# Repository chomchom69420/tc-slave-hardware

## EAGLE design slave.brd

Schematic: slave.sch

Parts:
3V1, 3V2, 3V3, 3V4, 3V5, 3V6, 3V7, 3V8, 3V9, 3V10, 3V11, 3V12, 3V13, 3V14, 3V15, 3V16, 3V17, 3V18, 3V19, 3V21: MCP40D17T-503E/LT; SC70-6_MC_MCH
C2: 100pF; C0603
C3, C4: 10uF; C0805
C5: 1uF; C0603
CB: 100nF; C0603
CEN, CEN1, CEN2, CEN3, CEN4, CEN5, CEN6, CEN7, CEN8, CEN9, CEN10, CEN11, CEN12, CEN13, CEN14, CEN15, CEN16, CEN17, CEN18, CEN19, CEN20: 100nF; C0603
CIN1, CIN2, CIN3: 10uF; C0805
COUT1, COUT2, COUT3, COUT4: 22uF; C1206
CSS: 47nF; C0603
CTON: 100pF; C0402
CVC: 4.7uF; C0402
D1, D2, D3, D4, D5, D6, D7, D11, D12, D13, D14, D15, D16, D17, D18, D19, D20, D21, D22, D23, D24, D25, D26, D27, D28, D29, D30, D31, D32, D33, D34, D35, D36, D37, D38, D39, D40, D41, D42, D43, D44, D45: VLMY1500-GS08; LED_1500-GS08_VIS
DEN: BZX84C5V1-7-F; SOT23
EN: CONN_HDR_1POS_0.1; 1X1
ESP_HDR_LEFT: PPTC191LFBN-RC; RHDR19W80P0X254_1X19_4876X254X
ESP_HDR_RIGHT: PPTC191LFBN-RC; RHDR19W80P0X254_1X19_4876X254X
FB: CONN_HDR_1POS_0.1; 1X1
J2, J3, J4, J5: EB21A-06-D; CONN_EB21A-06-D_ADM
J6, J7, J8: 282837-9; TE_282837-9
J9: 1715250000; CONN2_250000_WED
L1: 1.5uH; BCIH1367-2R2M
LX: CONN_HDR_1POS_0.1; 1X1
Q1, Q2, Q3, Q4, Q5, Q7, Q8, Q9, Q10, Q11, Q12, Q13, Q14, Q15, Q16, Q17, Q18, Q19, Q20, Q21, Q22, Q23, Q24, Q25, Q26, Q27, Q28, Q29, Q30, Q31, Q32, Q33, Q34, Q35, Q36, Q37, Q38, Q39, Q40, Q41, Q42: DMN2056U-7; SOT23
R1: 5.1k; R0603
R2: 27k; R0603
R3: 1k; R0402
R4, R8, R11, R12, R15, R19, R24, R28, R34, R37, R40, R43, R46, R49, R52, R55, R58, R61, R64, R67, R70, R73, R76, R79, R82, R85, R88, R91, R94, R97, R100, R103, R106, R109, R112, R115, R118, R121, R124, R127, R130: 220; R0603
R5, R6, R9, R13, R17, R20, R26, R29, R35, R38, R41, R44, R47, R50, R53, R56, R59, R62, R65, R68, R71, R74, R77, R80, R83, R86, R89, R92, R95, R98, R101, R104, R107, R110, R113, R116, R119, R122, R125, R128, R131: 150; R0603
R7, R10, R14, R18, R21, R25, R27, R30, R36, R39, R42, R45, R48, R51, R54, R57, R60, R63, R66, R69, R72, R75, R78, R81, R84, R87, R90, R93, R96, R99, R102, R105, R108, R111, R114, R117, R120, R123, R126, R129, R132: 6.8k; R0603
R16: 100R; PR-D2.7XL8.5MM
R22, R23: 0R; R0402
R31: 100k; R0402
R32, R33, R133, R134, R135, R136, R137, R138, R139, R140, R141, R142, R143, R144, R145, R146, R147, R148, R149, R171: CR-02JL6----1K; RES_CR-02_VKG
R169: RC0402FR-07698KL; RESC1005X40N
R170: RC0402FR-0782K5L; RC0402N_YAG
RECT: DBF310-13; DBF_DIO
REG: AOZ2255EQI-30; QFN_4X4_22L-EP2_S_AOS
REN: 1k; R0603
TON: CONN_HDR_1POS_0.1; 1X1
TP1, TP4, TP5: TPB1,27; B1,27
U1, U10, U11, U12, U13, U14, U15, U16, U17, U18, U19, U20, U21, U22, U23, U24, U25, U26, U27, U28: INA332AIDGKR; DGK0008A_N
U2: AP2112K-3.3TRG1; SOT_RG1_DIO
U3, U4, U5: MCP23008-E/P; DIP254P762X533-18
U6, U7, U8, U9: MC74HCT4851ADR2G; SOIC-16_ONS
U$1, U$2, U$4, U$5, U$6, U$7, U$8, U$9, U$10, U$11, U$12, U$13, U$14, U$15, U$16, U$17, U$18, U$19, U$20, U$21: YLR12-2-100F
VIN: CONN_HDR_1POS_0.1; 1X1

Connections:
3V3: 3V1.1 (VDD), 3V2.1 (VDD), 3V3.1 (VDD), 3V4.1 (VDD), 3V5.1 (VDD), 3V6.1 (VDD), 3V7.1 (VDD), 3V8.1 (VDD), 3V9.1 (VDD), 3V10.1 (VDD), 3V11.1 (VDD), 3V12.1 (VDD), 3V13.1 (VDD), 3V14.1 (VDD), 3V15.1 (VDD), 3V16.1 (VDD), 3V17.1 (VDD), 3V18.1 (VDD), 3V19.1 (VDD), 3V21.1 (VDD), C4.2, C5.2, ESP_HDR_LEFT.19, TP5.TP, U2.5 (VOUT)
5V0: ESP_HDR_LEFT.1
+5V: C2.2, C3.2, CEN1.2, CEN2.2, CEN3.2, CEN4.2, CEN5.2, CEN6.2, CEN7.2, CEN8.2, CEN9.2, CEN10.2, CEN11.2, CEN12.2, CEN13.2, CEN14.2, CEN15.2, CEN16.2, CEN17.2, CEN18.2, CEN19.2, CEN20.2, COUT1.2, COUT2.2, COUT3.2, COUT4.2, L1.P$2 (2), R2.1, R3.2, R16.2, R31.2, TP1.TP, U1.7 (V+), U1.8 (SD), U2.1 (VIN), U3.6 (*RESET), U3.18 (VDD), U4.5 (A0), U4.6 (*RESET), U4.18 (VDD), U5.4 (A1), U5.6 (*RESET), U5.18 (VDD), U6.16 (VCC), U7.16 (VCC), U8.16 (VCC), U9.16 (VCC), U10.7 (V+), U10.8 (SD), U11.7 (V+), U11.8 (SD), U12.7 (V+), U12.8 (SD), U13.7 (V+), U13.8 (SD), U14.7 (V+), U14.8 (SD), U15.7 (V+), U15.8 (SD), U16.7 (V+), U16.8 (SD), U17.7 (V+), U17.8 (SD), U18.7 (V+), U18.8 (SD), U19.7 (V+), U19.8 (SD), U20.7 (V+), U20.8 (SD), U21.7 (V+), U21.8 (SD), U22.7 (V+), U22.8 (SD), U23.7 (V+), U23.8 (SD), U24.7 (V+), U24.8 (SD), U25.7 (V+), U25.8 (SD), U26.7 (V+), U26.8 (SD), U27.7 (V+), U27.8 (SD), U28.7 (V+), U28.8 (SD)
+12V: J9.2, RECT.2
BST: CB.2, REG.20 (BST)
CS_SEL0: ESP_HDR_LEFT.5, U6.11 (A), U7.11 (A), U8.11 (A), U9.11 (A)
CS_SEL1: ESP_HDR_LEFT.7, U6.10 (B), U7.10 (B), U8.10 (B), U9.10 (B)
CS_SEL2: ESP_HDR_LEFT.8, U6.9 (C), U7.9 (C), U8.9 (C), U9.9 (C)
D0_A: R70.2, R71.2, U3.10 (GP0)
D0_A+: J8.8, Q22.P$2 (S)
D0_B: R73.2, R74.2, U3.11 (GP1)
D0_B+: J8.7, Q23.P$2 (S)
D0_C: R76.2, R77.2, U3.12 (GP2)
D0_C+: J8.6, Q24.P$2 (S)
D0_D: R79.2, R80.2, U3.13 (GP3)
D0_D+: J8.5, Q25.P$2 (S)
D0_E: R82.2, R83.2, U3.14 (GP4)
D0_E+: J8.4, Q26.P$2 (S)
D0_F: R100.2, R101.2, U3.15 (GP5)
D0_F+: J8.3, Q32.P$2 (S)
D0_G: R103.2, R104.2, U3.16 (GP6)
D0_G+: J8.2, Q33.P$2 (S)
D1_A: R85.2, R86.2, U4.10 (GP0)
D1_A+: J6.8, Q27.P$2 (S)
D1_B: R88.2, R89.2, U4.11 (GP1)
D1_B+: J6.7, Q28.P$2 (S)
D1_C: R91.2, R92.2, U4.12 (GP2)
D1_C+: J6.6, Q29.P$2 (S)
D1_D: R94.2, R95.2, U4.13 (GP3)
D1_D+: J6.5, Q30.P$2 (S)
D1_E: R97.2, R98.2, U4.14 (GP4)
D1_E+: J6.4, Q31.P$2 (S)
D1_F: R106.2, R107.2, U4.15 (GP5)
D1_F+: J6.3, Q34.P$2 (S)
D1_G: R109.2, R110.2, U4.16 (GP6)
D1_G+: J6.2, Q35.P$2 (S)
D2_A: R112.2, R113.2, U5.10 (GP0)
D2_A+: J7.8, Q36.P$2 (S)
D2_B: R115.2, R116.2, U5.11 (GP1)
D2_B+: J7.7, Q37.P$2 (S)
D2_C: R118.2, R119.2, U5.12 (GP2)
D2_C+: J7.6, Q38.P$2 (S)
D2_D: R121.2, R122.2, U5.13 (GP3)
D2_D+: J7.5, Q39.P$2 (S)
D2_E: R124.2, R125.2, U5.14 (GP4)
D2_E+: J7.4, Q40.P$2 (S)
D2_F: R127.2, R128.2, U5.15 (GP5)
D2_F+: J7.3, Q41.P$2 (S)
D2_G: R130.2, R131.2, U5.16 (GP6)
D2_G+: J7.2, Q42.P$2 (S)
EN: CEN.2, DEN.P$3 (C), EN.1, REG.1 (EN), REN.2
EN_F: R31.1, U2.3 (EN)
ESP_EN: ESP_HDR_LEFT.18
FB: FB.1, R1.1, R2.2, REG.2 (FB)
GND: 3V1.2 (VSS), 3V2.2 (VSS), 3V3.2 (VSS), 3V4.2 (VSS), 3V5.2 (VSS), 3V6.2 (VSS), 3V7.2 (VSS), 3V8.2 (VSS), 3V9.2 (VSS), 3V10.2 (VSS), 3V11.2 (VSS), 3V12.2 (VSS), 3V13.2 (VSS), 3V14.2 (VSS), 3V15.2 (VSS), 3V16.2 (VSS), 3V17.2 (VSS), 3V18.2 (VSS), 3V19.2 (VSS), 3V21.2 (VSS), C2.1, C3.1, C4.1, C5.1, CEN.1, CEN1.1, CEN2.1, CEN3.1, CEN4.1, CEN5.1, CEN6.1, CEN7.1, CEN8.1, CEN9.1, CEN11.1, CEN12.1, CEN13.1, CEN14.1, CEN15.1, CEN16.1, CEN17.1, CEN18.1, CEN19.1, CEN20.1, CIN1.1, CIN2.1, CIN3.1, COUT1.1, COUT2.1, COUT3.1, COUT4.1, CSS.2, CTON.2, CVC.2, D7.1, DEN.P$1 (A), ESP_HDR_LEFT.6, ESP_HDR_RIGHT.13, ESP_HDR_RIGHT.19, J2.1, J3.1, J4.1, J5.1, J6.1, J7.1, J8.1, R1.2, R7.1, R10.1, R14.1, R16.1, R18.1, R21.1, R23.1, R25.1, R27.1, R30.1, R36.1, R39.1, R42.1, R45.1, R48.1, R51.1, R54.1, R57.1, R60.1, R63.1, R66.1, R69.1, R72.1, R75.1, R78.1, R81.1, R84.1, R87.1, R90.1, R93.1, R96.1, R99.1, R102.1, R105.1, R108.1, R111.1, R114.1, R117.1, R120.1, R123.1, R126.1, R129.1, R132.1, RECT.3, REG.3 (AGND), REG.12 (PGND_2), REG.13 (PGND_3), REG.14 (PGND_4), REG.15 (PGND), TP4.TP, U1.4 (V-), U2.2 (GND), U3.3 (A2), U3.4 (A1), U3.5 (A0), U3.9 (VSS), U4.3 (A2), U4.4 (A1), U4.9 (VSS), U5.3 (A2), U5.5 (A0), U5.9 (VSS), U6.2 (X6), U6.4 (X7), U6.5 (X5), U6.6 (ENABLE), U6.8 (GND), U7.2 (X6), U7.4 (X7), U7.5 (X5), U7.6 (ENABLE), U7.8 (GND), U8.2 (X6), U8.4 (X7), U8.5 (X5), U8.6 (ENABLE), U8.8 (GND), U9.2 (X6), U9.4 (X7), U9.5 (X5), U9.6 (ENABLE), U9.8 (GND), U10.4 (V-), U11.4 (V-), U12.4 (V-), U13.4 (V-), U14.4 (V-), U15.4 (V-), U16.4 (V-), U17.4 (V-), U18.4 (V-), U19.4 (V-), U20.4 (V-), U21.4 (V-), U22.4 (V-), U23.4 (V-), U24.4 (V-), U25.4 (V-), U26.4 (V-), U27.4 (V-), U28.4 (V-)
GPIO1: ESP_HDR_RIGHT.16
GPIO3: ESP_HDR_RIGHT.15
GPIO6: ESP_HDR_RIGHT.1
GPIO7: ESP_HDR_RIGHT.2
GPIO8: ESP_HDR_RIGHT.3
GPIO9: ESP_HDR_LEFT.4
GPIO10: ESP_HDR_LEFT.3
GPIO11: ESP_HDR_LEFT.2
I_OA: 3V17.6 (W), U7.14 (X1), U26.6 (VOUT)
I_OGF: 3V6.6 (W), U7.15 (X2), U14.6 (VOUT)
I_OGL: 3V18.6 (W), U7.12 (X3), U27.6 (VOUT)
I_OGR: 3V7.6 (W), U7.1 (X4), U15.6 (VOUT)
I_OR: 3V5.6 (W), U7.13 (X0), U13.6 (VOUT)
I_PA: 3V12.6 (W), U6.14 (X1), U21.6 (VOUT)
I_PGF: 3V1.6 (W), U1.6 (VOUT), U6.15 (X2)
I_PGL: 3V13.6 (W), U6.12 (X3), U22.6 (VOUT)
I_PGR: 3V2.6 (W), U6.1 (X4), U10.6 (VOUT)
I_PR: 3V21.6 (W), U6.13 (X0), U19.6 (VOUT)
I_SA: 3V3.6 (W), U8.14 (X1), U11.6 (VOUT)
I_SGF: 3V15.6 (W), U8.15 (X2), U24.6 (VOUT)
I_SGL: 3V4.6 (W), U8.12 (X3), U12.6 (VOUT)
I_SGR: 3V16.6 (W), U8.1 (X4), U25.6 (VOUT)
I_SPA: 3V8.6 (W), U9.14 (X1), U16.6 (VOUT)
I_SPGF: 3V10.6 (W), U9.15 (X2), U18.6 (VOUT)
I_SPGL: 3V9.6 (W), U9.12 (X3), U17.6 (VOUT)
I_SPGR: 3V11.6 (W), U9.1 (X4), U20.6 (VOUT)
I_SPR: 3V19.6 (W), U9.13 (X0), U28.6 (VOUT)
I_SR: 3V14.6 (W), U8.13 (X0), U23.6 (VOUT)
JP2: D1.1, D2.1, D3.1, D4.1, D5.1, D6.1, D11.1, D12.1, D13.1, D14.1, D15.1, D16.1, D17.1, D18.1, D19.1, D20.1, D21.1, D22.1, D23.1, D24.1, D25.1, D26.1, D27.1, D28.1, D29.1, D30.1, D31.1, D32.1, D33.1, D34.1, D35.1, D36.1, D37.1, D38.1, D39.1, D40.1, D41.1, D42.1, D43.1, D44.1, D45.1, R23.2
LX: CB.1, L1.P$1 (1), LX.1, REG.10 (LX_2), REG.16 (LX_3), REG.17 (LX_4), REG.18 (LX)
unnamed: D2.2, R6.1
unnamed: R3.1, R22.2
unnamed: D7.2, R22.1
unnamed: 3V21.5 (B), R171.1, U19.1 (RG)
unnamed: 3V1.5 (B), R32.1, U1.1 (RG)
unnamed: R32.2, U1.5 (REF)
unnamed: D3.2, R9.1
unnamed: J9.1, RECT.4
unnamed: 3V2.5 (B), R33.1, U10.1 (RG)
unnamed: R33.2, U10.5 (REF)
unnamed: 3V3.5 (B), R133.1, U11.1 (RG)
unnamed: R171.2, U19.5 (REF)
unnamed: R133.2, U11.5 (REF)
unnamed: D1.2, R5.1
unnamed: 3V4.5 (B), R134.1, U12.1 (RG)
unnamed: R134.2, U12.5 (REF)
unnamed: D4.2, R13.1
unnamed: 3V5.5 (B), R135.1, U13.1 (RG)
unnamed: R135.2, U13.5 (REF)
unnamed: D5.2, R17.1
unnamed: 3V6.5 (B), R136.1, U14.1 (RG)
unnamed: R136.2, U14.5 (REF)
unnamed: D6.2, R20.1
unnamed: 3V7.5 (B), R137.1, U15.1 (RG)
unnamed: R137.2, U15.5 (REF)
unnamed: D11.2, R26.1
unnamed: 3V8.5 (B), R138.1, U16.1 (RG)
unnamed: R138.2, U16.5 (REF)
unnamed: 3V9.5 (B), R139.1, U17.1 (RG)
unnamed: R139.2, U17.5 (REF)
unnamed: 3V10.5 (B), R140.1, U18.1 (RG)
unnamed: R140.2, U18.5 (REF)
unnamed: 3V11.5 (B), R141.1, U20.1 (RG)
unnamed: R141.2, U20.5 (REF)
unnamed: 3V12.5 (B), R142.1, U21.1 (RG)
unnamed: R142.2, U21.5 (REF)
unnamed: 3V13.5 (B), R143.1, U22.1 (RG)
unnamed: R143.2, U22.5 (REF)
unnamed: 3V14.5 (B), R144.1, U23.1 (RG)
unnamed: R144.2, U23.5 (REF)
unnamed: 3V15.5 (B), R145.1, U24.1 (RG)
unnamed: R145.2, U24.5 (REF)
unnamed: 3V16.5 (B), R146.1, U25.1 (RG)
unnamed: R146.2, U25.5 (REF)
unnamed: 3V17.5 (B), R147.1, U26.1 (RG)
unnamed: R147.2, U26.5 (REF)
unnamed: 3V18.5 (B), R148.1, U27.1 (RG)
unnamed: R148.2, U27.5 (REF)
unnamed: 3V19.5 (B), R149.1, U28.1 (RG)
unnamed: R149.2, U28.5 (REF)
unnamed: R169.1, R170.2
unnamed: D12.2, R29.1
unnamed: D13.2, R35.1
unnamed: D14.2, R38.1
unnamed: D15.2, R41.1
unnamed: D16.2, R44.1
unnamed: D17.2, R47.1
unnamed: D18.2, R50.1
unnamed: D19.2, R53.1
unnamed: D20.2, R56.1
unnamed: D21.2, R59.1
unnamed: D22.2, R62.1
unnamed: D23.2, R65.1
unnamed: D24.2, R68.1
unnamed: D25.2, R71.1
unnamed: D26.2, R74.1
unnamed: D27.2, R77.1
unnamed: D28.2, R80.1
unnamed: D29.2, R83.1
unnamed: D30.2, R86.1
unnamed: D31.2, R89.1
unnamed: D32.2, R92.1
unnamed: D33.2, R95.1
unnamed: D34.2, R98.1
unnamed: D35.2, R101.1
unnamed: D36.2, R104.1
unnamed: D37.2, R107.1
unnamed: D38.2, R110.1
unnamed: D39.2, R113.1
unnamed: D40.2, R116.1
unnamed: D41.2, R119.1
unnamed: D42.2, R122.1
unnamed: D43.2, R125.1
unnamed: D44.2, R128.1
unnamed: D45.2, R131.1
OA+: J4.5, U26.2 (VIN-), U$15.P$2
OA++: Q13.P$2 (S), U26.3 (VIN+), U$15.P$1
OGF+: J4.4, U14.2 (VIN-), U$14.P$2
OGF++: Q14.P$2 (S), U14.3 (VIN+), U$14.P$1
OGL+: J4.3, U27.2 (VIN-), U$13.P$2
OGL++: Q15.P$2 (S), U27.3 (VIN+), U$13.P$1
OGR+: J4.2, U15.2 (VIN-), U$12.P$2
OGR++: Q16.P$2 (S), U15.3 (VIN+), U$12.P$1
OR+: J4.6, U13.2 (VIN-), U$16.P$2
OR++: Q12.P$2 (S), U13.3 (VIN+), U$16.P$1
O_CURRENT: ESP_HDR_LEFT.16, U7.3 (X)
PA: ESP_HDR_LEFT.10, R4.2, R6.2, R43.2, R44.2
PA+: J2.5, U21.2 (VIN-), U$2.P$2
PA++: Q2.P$2 (S), U21.3 (VIN+), U$2.P$1
PGF: ESP_HDR_LEFT.11, R8.2, R9.2, R46.2, R47.2
PGF+: J2.4, U1.2 (VIN-), U$4.P$2
PGF++: Q3.P$2 (S), U1.3 (VIN+), U$4.P$1
PGL: ESP_HDR_LEFT.12, R12.2, R13.2, R49.2, R50.2
PGL+: J2.3, U22.2 (VIN-), U$5.P$2
PGL++: Q4.P$2 (S), U22.3 (VIN+), U$5.P$1
PGR: ESP_HDR_LEFT.13, R15.2, R17.2, R52.2, R53.2
PGR+: J2.2, U10.2 (VIN-), U$6.P$2
PGR++: Q5.P$2 (S), U10.3 (VIN+), U$6.P$1
PR: ESP_HDR_LEFT.9, R5.2, R11.2, R40.2, R41.2
PR+: J2.6, U19.2 (VIN-), U$1.P$2
PR++: Q1.P$2 (S), U19.3 (VIN+), U$1.P$1
P_CURRENT: ESP_HDR_LEFT.14, U6.3 (X)
Q1G: Q1.P$1 (G), R11.1, R25.2
Q1G1: Q2.P$1 (G), R4.1, R7.2
Q1G2: Q3.P$1 (G), R8.1, R10.2
Q1G3: Q4.P$1 (G), R12.1, R14.2
Q1G4: Q5.P$1 (G), R15.1, R18.2
Q1G5: Q7.P$1 (G), R19.1, R21.2
Q1G6: Q8.P$1 (G), R24.1, R27.2
Q1G7: Q9.P$1 (G), R28.1, R30.2
Q1G8: Q10.P$1 (G), R34.1, R36.2
Q1G9: Q11.P$1 (G), R37.1, R39.2
Q1G10: Q12.P$1 (G), R40.1, R42.2
Q1G11: Q13.P$1 (G), R43.1, R45.2
Q1G12: Q14.P$1 (G), R46.1, R48.2
Q1G13: Q15.P$1 (G), R49.1, R51.2
Q1G14: Q16.P$1 (G), R52.1, R54.2
Q1G15: Q17.P$1 (G), R55.1, R57.2
Q1G16: Q18.P$1 (G), R58.1, R60.2
Q1G17: Q19.P$1 (G), R61.1, R63.2
Q1G18: Q20.P$1 (G), R64.1, R66.2
Q1G19: Q21.P$1 (G), R67.1, R69.2
Q1G20: Q22.P$1 (G), R70.1, R72.2
Q1G21: Q23.P$1 (G), R73.1, R75.2
Q1G22: Q24.P$1 (G), R76.1, R78.2
Q1G23: Q25.P$1 (G), R79.1, R81.2
Q1G24: Q26.P$1 (G), R82.1, R84.2
Q1G25: Q27.P$1 (G), R85.1, R87.2
Q1G26: Q28.P$1 (G), R88.1, R90.2
Q1G27: Q29.P$1 (G), R91.1, R93.2
Q1G28: Q30.P$1 (G), R94.1, R96.2
Q1G29: Q31.P$1 (G), R97.1, R99.2
Q1G30: Q32.P$1 (G), R100.1, R102.2
Q1G31: Q33.P$1 (G), R103.1, R105.2
Q1G32: Q34.P$1 (G), R106.1, R108.2
Q1G33: Q35.P$1 (G), R109.1, R111.2
Q1G34: Q36.P$1 (G), R112.1, R114.2
Q1G35: Q37.P$1 (G), R115.1, R117.2
Q1G36: Q38.P$1 (G), R118.1, R120.2
Q1G37: Q39.P$1 (G), R121.1, R123.2
Q1G38: Q40.P$1 (G), R124.1, R126.2
Q1G39: Q41.P$1 (G), R127.1, R129.2
Q1G40: Q42.P$1 (G), R130.1, R132.2
SA: ESP_HDR_RIGHT.9, R24.2, R26.2
SA+: J3.5, U11.2 (VIN-), U$8.P$2
SA++: Q8.P$2 (S), U11.3 (VIN+), U$8.P$1
SCL: 3V1.3 (SCL), 3V2.3 (SCL), 3V3.3 (SCL), 3V4.3 (SCL), 3V5.3 (SCL), 3V6.3 (SCL), 3V7.3 (SCL), 3V8.3 (SCL), 3V9.3 (SCL), 3V10.3 (SCL), 3V11.3 (SCL), 3V12.3 (SCL), 3V13.3 (SCL), 3V14.3 (SCL), 3V15.3 (SCL), 3V16.3 (SCL), 3V17.3 (SCL), 3V18.3 (SCL), 3V19.3 (SCL), 3V21.3 (SCL), ESP_HDR_RIGHT.17, U3.1 (SCL), U4.1 (SCL), U5.1 (SCL)
SDA: 3V1.4 (SDA), 3V2.4 (SDA), 3V3.4 (SDA), 3V4.4 (SDA), 3V5.4 (SDA), 3V6.4 (SDA), 3V7.4 (SDA), 3V8.4 (SDA), 3V9.4 (SDA), 3V10.4 (SDA), 3V11.4 (SDA), 3V12.4 (SDA), 3V13.4 (SDA), 3V14.4 (SDA), 3V15.4 (SDA), 3V16.4 (SDA), 3V17.4 (SDA), 3V18.4 (SDA), 3V19.4 (SDA), 3V21.4 (SDA), ESP_HDR_RIGHT.14, U3.2 (SDA), U4.2 (SDA), U5.2 (SDA)
SGF: ESP_HDR_RIGHT.10, R28.2, R29.2
SGF+: J3.4, U24.2 (VIN-), U$9.P$2
SGF++: Q9.P$2 (S), U24.3 (VIN+), U$9.P$1
SGL: ESP_HDR_RIGHT.11, R34.2, R35.2
SGL+: J3.3, U12.2 (VIN-), U$10.P$2
SGL++: Q10.P$2 (S), U12.3 (VIN+), U$10.P$1
SGR: ESP_HDR_RIGHT.12, R37.2, R38.2
SGR+: J3.2, U25.2 (VIN-), U$11.P$2
SGR++: Q11.P$2 (S), U25.3 (VIN+), U$11.P$1
SPA: ESP_HDR_RIGHT.5, R58.2, R59.2
SPA+: J5.5, U16.2 (VIN-), U$18.P$2
SPA++: Q18.P$2 (S), U16.3 (VIN+), U$18.P$1
SPGF: ESP_HDR_RIGHT.6, R61.2, R62.2
SPGF+: J5.4, U18.2 (VIN-), U$19.P$2
SPGF++: Q19.P$2 (S), U18.3 (VIN+), U$19.P$1
SPGL: ESP_HDR_RIGHT.7, R64.2, R65.2
SPGL+: J5.3, U17.2 (VIN-), U$20.P$2
SPGL++: Q20.P$2 (S), U17.3 (VIN+), U$20.P$1
SPGR: ESP_HDR_RIGHT.8, R67.2, R68.2
SPGR+: J5.2, U20.2 (VIN-), U$21.P$2
SPGR++: Q21.P$2 (S), U20.3 (VIN+), U$21.P$1
SPR: ESP_HDR_RIGHT.4, R55.2, R56.2
SPR+: J5.6, U28.2 (VIN-), U$17.P$2
SPR++: Q17.P$2 (S), U28.3 (VIN+), U$17.P$1
SP_CURRENT: ESP_HDR_LEFT.17, U9.3 (X)
SR: ESP_HDR_RIGHT.18, R19.2, R20.2
SR+: J3.6, U23.2 (VIN-), U$7.P$2
SR++: Q7.P$2 (S), U23.3 (VIN+), U$7.P$1
SS: CSS.1, REG.22 (SS)
S_CURRENT: ESP_HDR_LEFT.15, U8.3 (X)
TON: CTON.1, R170.1, REG.19 (TON), TON.1
VCC: CVC.1, REG.21 (VCC)
VIN: CIN1.2, CIN2.2, CIN3.2, J6.9, J7.9, J8.9, Q1.P$3 (D), Q2.P$3 (D), Q3.P$3 (D), Q4.P$3 (D), Q5.P$3 (D), Q7.P$3 (D), Q8.P$3 (D), Q9.P$3 (D), Q10.P$3 (D), Q11.P$3 (D), Q12.P$3 (D), Q13.P$3 (D), Q14.P$3 (D), Q15.P$3 (D), Q16.P$3 (D), Q17.P$3 (D), Q18.P$3 (D), Q19.P$3 (D), Q20.P$3 (D), Q21.P$3 (D), Q22.P$3 (D), Q23.P$3 (D), Q24.P$3 (D), Q25.P$3 (D), Q26.P$3 (D), Q27.P$3 (D), Q28.P$3 (D), Q29.P$3 (D), Q30.P$3 (D), Q31.P$3 (D), Q32.P$3 (D), Q33.P$3 (D), Q34.P$3 (D), Q35.P$3 (D), Q36.P$3 (D), Q37.P$3 (D), Q38.P$3 (D), Q39.P$3 (D), Q40.P$3 (D), Q41.P$3 (D), Q42.P$3 (D), R169.2, RECT.1, REG.6 (AIN), REG.7 (IN), REN.1, VIN.1

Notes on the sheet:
Power Input and Regulation
Power to ESP32 (via 3V3 REG)
Primary
Secondary
Overhead
Spare
Timer Digit 0 FETs and Port
Timer Digit 1 FETs and Port
Timer Digit 2 FETs and Port

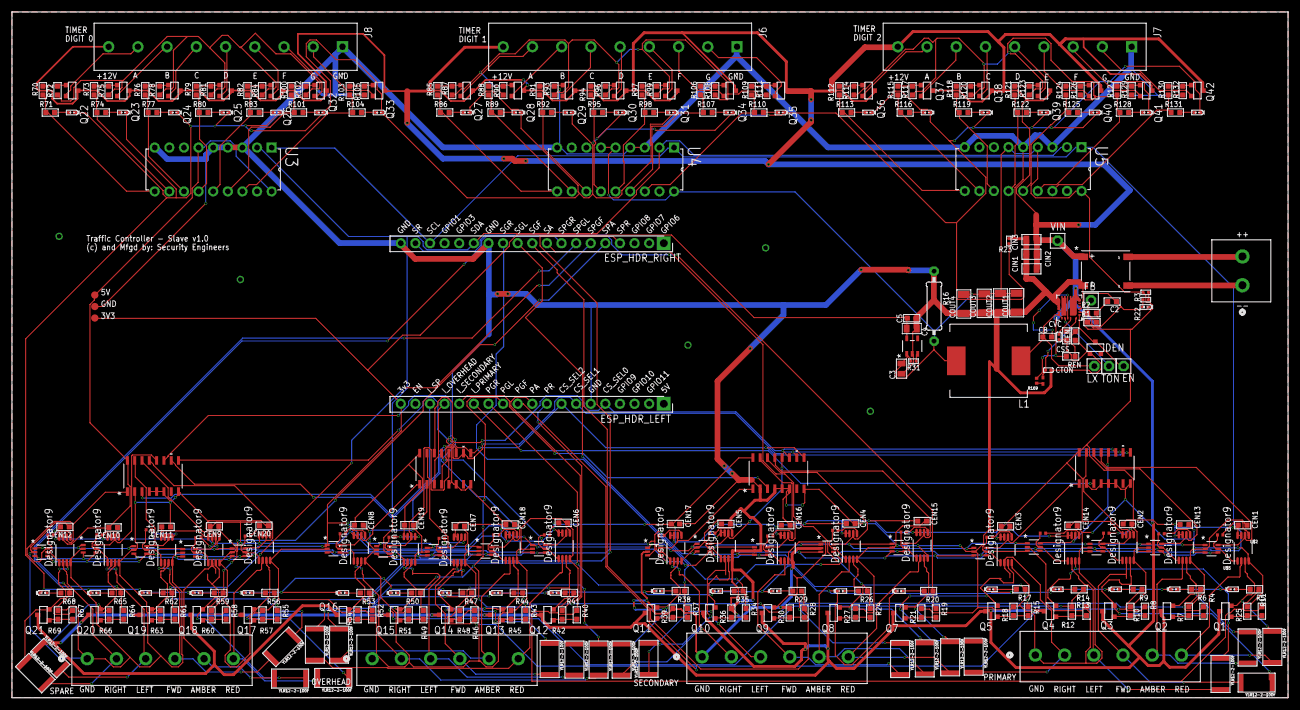
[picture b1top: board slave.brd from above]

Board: 2 copper layers, 221.8 x 119.2 mm, 362 parts (0 on the bottom side), 266 nets.

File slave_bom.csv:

Comment,Designator,Footprint,LCSC Part #
0R,R22 R23,R0402,
1.5uH,L1,BCIH1367-2R2M,
1k,R3,R0402,
1k,REN,R0603,
1uF,C5,C0603,
4.7uF,CVC,C0402,
5.1k,R1,R0603,
6.8k,R7 R10 R14 R18 R21 R25 R27 R30 R36 R39 R42 R45 R48 R51 R54 R57 R60 R63 R66 R69 R72 R75 R78 R81 R84 R87 R90 R93 R96 R99 R102 R105 R108 R111 R114 R117 R120 R123 R126 R129 R132,R0603,
10uF,C3 C4 CIN1 CIN2 CIN3,C0805,
22uF,COUT1 COUT2 COUT3 COUT4,C1206,
27k,R2,R0603,
47nF,CSS,C0603,
100k,R31,R0402,
100nF,CB CEN CEN1 CEN2 CEN3 CEN4 CEN5 CEN6 CEN7 CEN8 CEN9 CEN10 CEN11 CEN12 CEN13 CEN14 CEN15 CEN16 CEN17 CEN18 CEN19 CEN20,C0603,
100pF,CTON,C0402,
100pF,C2,C0603,
150,R5 R6 R9 R13 R17 R20 R26 R29 R35 R38 R41 R44 R47 R50 R53 R56 R59 R62 R65 R68 R71 R74 R77 R80 R83 R86 R89 R92 R95 R98 R101 R104 R107 R110 R113 R116 R119 R122 R125 R128 R131,R0603,
220,R4 R8 R11 R12 R15 R19 R24 R28 R34 R37 R40 R43 R46 R49 R52 R55 R58 R61 R64 R67 R70 R73 R76 R79 R82 R85 R88 R91 R94 R97 R100 R103 R106 R109 R112 R115 R118 R121 R124 R127 R130,R0603,
282837-9,J6 J7 J8,TE_282837-9,
1715250000,J9,CONN2_250000_WED,
AOZ2255EQI-30,REG,QFN_4X4_22L-EP2_S_AOS,
AP2112K-3.3TRG1,U2,SOT_RG1_DIO,
BZX84C5V1-7-F,DEN,SOT23,
CR-02JL6----1K,R32 R33 R133 R134 R135 R136 R137 R138 R139 R140 R141 R142 R143 R144 R145 R146 R147 R148 R149 R171,RES_CR-02_VKG,
DBF310-13,RECT,DBF_DIO,
DMN2056U-7,Q1 Q2 Q3 Q4 Q5 Q7 Q8 Q9 Q10 Q11 Q12 Q13 Q14 Q15 Q16 Q17 Q18 Q19 Q20 Q21 Q22 Q23 Q24 Q25 Q26 Q27 Q28 Q29 Q30 Q31 Q32 Q33 Q34 Q35 Q36 Q37 Q38 Q39 Q40 Q41 Q42,SOT23,
INA332AIDGKR,U1 U10 U11 U12 U13 U14 U15 U16 U17 U18 U19 U20 U21 U22 U23 U24 U25 U26 U27 U28,DGK0008A_N,
MC74HCT4851ADR2G,U6 U7 U8 U9,SOIC-16_ONS,
MCP40D17T-503E/LT,3V1 3V2 3V3 3V4 3V5 3V6 3V7 3V8 3V9 3V10 3V11 3V12 3V13 3V14 3V15 3V16 3V17 3V18 3V19 3V21,SC70-6_MC_MCH,
MCP23008-E/P,U3 U4 U5,DIP254P762X533-18,
RC0402FR-0782K5L,R170,RC0402N_YAG,
RC0402FR-07698KL,R169,RESC1005X40N,
VLMY1500-GS08,D1 D2 D3 D4 D5 D6 D7 D11 D12 D13 D14 D15 D16 D17 D18 D19 D20 D21 D22 D23 D24 D25 D26 D27 D28 D29 D30 D31 D32 D33 D34 D35 D36 D37 D38 D39 D40 D41 D42 D43 D44 D45,LED_1500-GS08_VIS,
YLR12-2-100F,U$1 U$2 U$4 U$5 U$6 U$7 U$8 U$9 U$10 U$11 U$12 U$13 U$14 U$15 U$16 U$17 U$18 U$19 U$20 U$21,YLR12-2-100F,

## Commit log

2023-08-10 init commit
2023-08-11 added 6 pin screw terminal Lamp ports
2023-08-16 schematic finalized
2023-08-19 removed backup files, finalized board layoout
2023-08-19 removed files named master (old files)
2023-08-20 changed header, but clearance issues
2023-08-22 fixed trace widths of lamp mos and current sensor power traces
2023-08-24 fixed GND labels for individual ports and FETs, rerouted. Fixed GND thickness in MOS sides, Put labels, Combined overhead and primary esp pin nets
2023-08-29 added jlc and pcbpower cpl and bom files, added gerber files zip
2023-09-08 made v1.2 of slave boards, replaced current sensors by I to V converter using digital pot
2023-09-09 finished v1.1 board and schematic design with Instrumentation amplifier and shunt
2023-09-09 updated RTON 781.25k resistor with series of 698k and 82.5k resistors, generated gerber and bom, cpl files
2023-09-09 removed old gerber zip
2023-09-09 removed old sch and board for v1.1
2023-09-10 updated bom
2023-09-13 added new 100 mOhm shunt resistor for current sensing

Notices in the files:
parts and their libraries:
COPYRIGHT: Copyright (C) 2022 Ultra Librarian. All rights reserved.
COPYRIGHT: Copyright (C) 2023 Ultra Librarian. All rights reserved.
